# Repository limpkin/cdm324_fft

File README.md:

# CDM324 v2 FFT Project
This repository contains the source files created for the making of the CDM324 project described on <a href="https://www.limpkin.fr/index.php?post/2022/03/31/CDM324-Doppler-Motion-Sensor-Backpack%2C-now-with-FFTs%21">limpkin.fr</a>  
The assembly may be purchased here: <a href="https://www.tindie.com/products/stephanelec/cdm324-doppler-speed-sensor/">US shop</a> / <a href="https://lectronz.com/products/cdm324-doppler-speed-sensor">EU shop</a>   

## Repository Structure
- <b>datasheets</b>: main components datasheets
- <b>fw</b>: firmware source files, used in STM32CubeIDE
- <b>kicad</b>: kicad source files for the "backpack" (cdm324_v2) and the "expansion board" (cdm324_exp)
- <b>scripts</b>: python source files for the tools that are used together with the expansion board

## Quick Interfacing Guide (to be completed)

### Unit change to km/h  
To change the speed readout to km/h, connect the "PA1/KMH" pad to the "GND" pad in the above diagram.  

### UART connection  
**The UART connection is 3V3 and NOT 5V.**  
To connect the device to an external platform through UART, please use the MCU UART RX/TX pins shown above.   
The baud rate is **1Mbit/s**, speed **can be queried** by **sending the 'k'** character for km/h or the 'm' character for mph.  
**In case of doubt about the UART connection, reboot the device**: it should output "CDM324 fw....".  
**Make sure your host device can handle 1MBit/s**. If that's not the case, head to the [release section](https://github.com/limpkin/cdm324_fft/releases) to download firmware with different UART baud rates.  
Finally, if you still have doubts about the UART connection, you may connect one of your host platform GPIO to the nRESET pin and reset the CDM324 device at your host platform boot.  

## Reflashing the Device

In the unlikely case you want to reflash your device with another firmware, you may either use the [GUI present in this repository](https://github.com/limpkin/cdm324_fft/tree/main/scripts) or the [stm32loader python module](https://pypi.org/project/stm32loader/) directly :  

> pip install stm32loader
> 
... then with the expansion board connected to the device (**as it uses RTS/CTS signals to control the MCU nRESET and BOOT0 pins**):  

> stm32loader -b 115200 -p  com_port -e -w -v -s -f F3 updatefile.bin

If you don't have the companion expansion board, you may use [STM32 Flash loader](https://www.st.com/en/development-tools/flasher-stm32.html) after performing the following toggling sequence:  
- tie nRESET to GND  
- bring BOOT0 to 3V3_OUT  
- release nRESET  
- releae BOOT0  

## Sample Arduino code to fetch speed from device

```c
#define RESET_PIN 2

void issue_cdm324_reset()
{  
  bool string_received = false;
  char receive_buffer[50];
  int index = 0;

  // 20ms reset
  pinMode(RESET_PIN, OUTPUT);
  delay(20);
  pinMode(RESET_PIN, INPUT);

  // get string
  while (string_received == false)
  {
    if (Serial1.available() > 0)
    {
      char bla = Serial1.read();
      receive_buffer[index++] = bla;
      if (bla == '\n')
        string_received = true;
    }
  }
  receive_buffer[index] = 0;

  Serial.println("Received from the CDM324:");
  Serial.println(receive_buffer);
}

void setup() 
{
  // Local console
  Serial.begin(115200);
  Serial.println("Hello there!");

  // To the CDM324
  Serial1.begin(57600);

  // Reset CDM324
  pinMode(RESET_PIN, INPUT);
  digitalWrite(RESET_PIN, LOW);
  issue_cdm324_reset();
}

float get_speed(bool kmh)
{
  if (kmh == true)
  {
    // Query km/h * 10
    Serial1.print('k');
  }
  else
  {
    // Query mph * 10
    Serial1.print('m');
  }  
  while(Serial1.available() == 0);
  float speed = Serial1.parseFloat();
  return (speed / 10);
}

void loop()
{
  Serial.println(get_speed(false));
  delay(500);
}
```

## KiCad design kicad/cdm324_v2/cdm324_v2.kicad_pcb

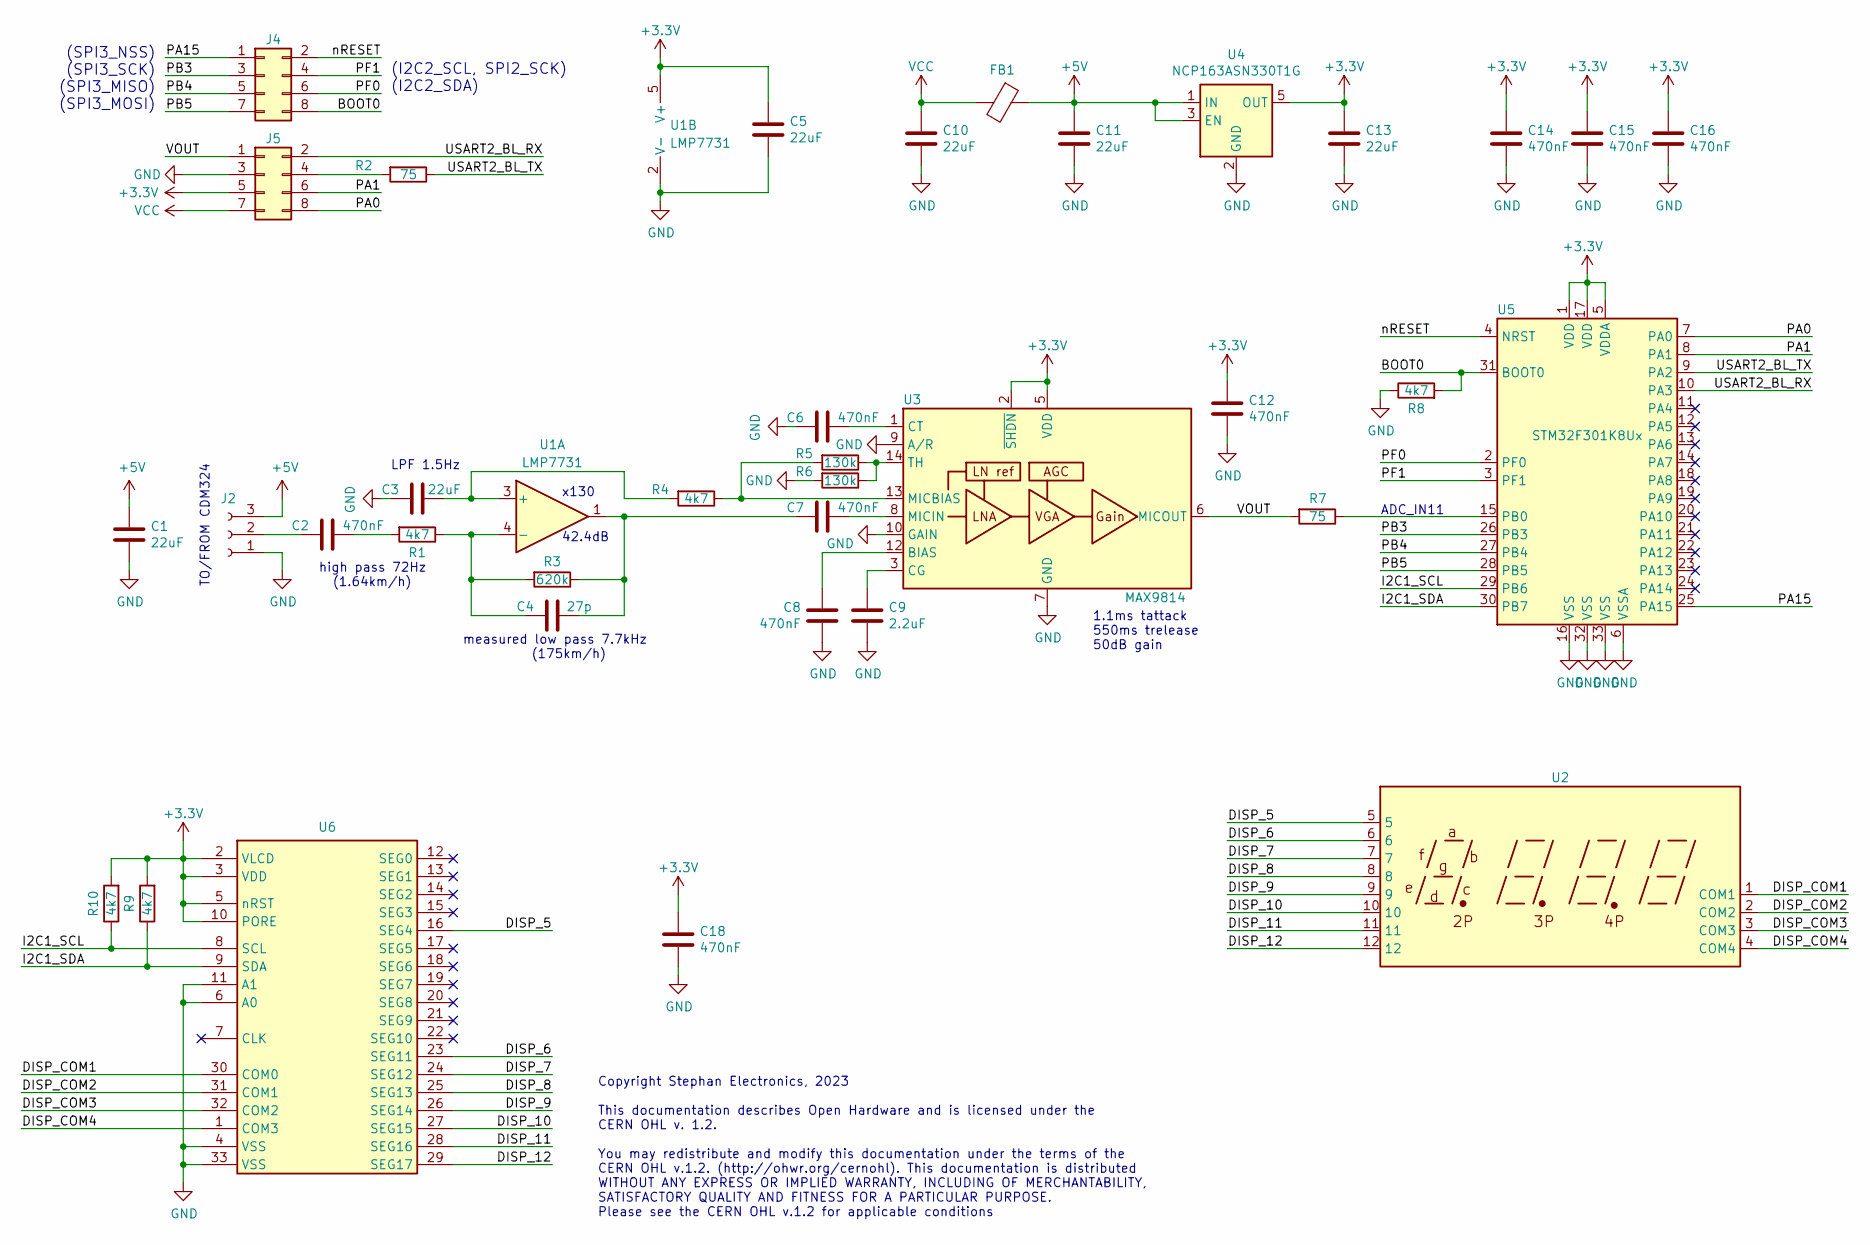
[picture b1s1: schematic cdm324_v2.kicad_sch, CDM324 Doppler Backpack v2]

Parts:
C1, C3, C5, C10, C11, C13: 22uF; C_0805_2012Metric
C2, C6, C7, C8, C12, C14, C15, C16, C18: 470nF; C_0402_1005Metric
C4: 27p; C_0603_1608Metric
C9: 2.2uF; C_0603_1608Metric
FB1: Ferrite_Bead; L_0805_2012Metric
J2: Conn_01x03_Female; PinHeader_1x03_P2.54mm_Vertical
J4, J5: Conn_02x04_Odd_Even; PinSocket_2x04_P2.54mm_Vertical
R1, R4, R8, R9, R10: 4k7; R_0603_1608Metric
R2, R7: 75; R_0402_1005Metric
R3: 620k; R_0603_1608Metric
R5, R6: 130k; R_0603_1608Metric
U1: LMP7731; SOT-23-5
U2: TN_DISPLAY
U3: MAX9814; DFN-14-1EP_3x3mm_P0.4mm_EP1.78x2.35mm
U4: NCP163ASN330T1G; SOT-23-5
U5: STM32F301K8Ux; QFN-32-1EP_5x5mm_P0.5mm_EP3.45x3.45mm
U6: QFN-32-1EP_5x5mm_P0.5mm_EP3.65x3.65mm

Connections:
+3V3: C5.1, C12.1, C13.1, C14.1, C15.1, C16.1, C18.1, J5.5, R9.2, R10.2, U1.5 (V+), U3.2 (~SHDN), U3.5 (VDD), U4.5 (OUT), U5.1 (VDD), U5.5 (VDDA), U5.17 (VDD), U6.2 (VLCD), U6.3 (VDD), U6.5 (nRST), U6.10 (PORE)
+5V: C1.1, C11.1, FB1.1, J2.3, U4.1 (IN), U4.3 (EN)
/BOOT0: J4.8, R8.2, U5.31 (BOOT0)
/DISP_5: U2.5, U6.16 (SEG4)
/DISP_6: U2.6, U6.23 (SEG11)
/DISP_7: U2.7, U6.24 (SEG12)
/DISP_8: U2.8, U6.25 (SEG13)
/DISP_9: U2.9, U6.26 (SEG14)
/DISP_10: U2.10, U6.27 (SEG15)
/DISP_11: U2.11, U6.28 (SEG16)
/DISP_12: U2.12, U6.29 (SEG17)
/DISP_COM1: U2.1 (COM1), U6.30 (COM0)
/DISP_COM2: U2.2 (COM2), U6.31 (COM1)
/DISP_COM3: U2.3 (COM3), U6.32 (COM2)
/DISP_COM4: U2.4 (COM4), U6.1 (COM3)
/I2C1_SCL: R10.1, U5.29 (PB6), U6.8 (SCL)
/I2C1_SDA: R9.1, U5.30 (PB7), U6.9 (SDA)
/PA0: J5.8, U5.7 (PA0)
/PA1: J5.6, U5.8 (PA1)
/PA15: J4.1, U5.25 (PA15)
/PB3: J4.3, U5.26 (PB3)
/PB4: J4.5, U5.27 (PB4)
/PB5: J4.7, U5.28 (PB5)
/PF0: J4.6, U5.2 (PF0)
/PF1: J4.4, U5.3 (PF1)
/USART2_BL_RX: J5.2, U5.10 (PA3)
/USART2_BL_TX: R2.1, U5.9 (PA2)
/VOUT: J5.1, R7.2, U3.6 (MICOUT)
/nRESET: J4.2, U5.4 (NRST)
GND: C1.2, C3.2, C5.2, C6.2, C8.2, C9.2, C10.2, C11.2, C12.2, C13.2, C14.2, C15.2, C16.2, C18.2, J2.1, J5.3, R6.2, R8.1, U1.2 (V-), U3.4 (GND), U3.7 (GND), U3.9 (A/R), U3.10 (GAIN), U3.11 (GND), U3.15 (GND), U4.2 (GND), U5.6 (VSSA), U5.16 (VSS), U5.32 (VSS), U5.33 (VSS), U6.4 (VSS), U6.6 (A0), U6.11 (A1), U6.33 (VSS)
unnamed: C2.1, R1.2
unnamed: C4.1, C7.2, R3.1, U1.1
unnamed: C2.2, J2.2
unnamed: J5.4, R2.2
unnamed: C3.1, R4.2, U1.3 (+)
unnamed: C4.2, R1.1, R3.2, U1.4 (-)
unnamed: C8.1, U3.12 (BIAS)
unnamed: C9.1, U3.3 (CG)
unnamed: C6.1, U3.1 (CT)
unnamed: R4.1, R5.2, U3.13 (MICBIAS)
unnamed: C7.1, U3.8 (MICIN)
unnamed: R5.1, R6.1, U3.14 (TH)
unnamed: R7.1, U5.15 (PB0)
VCC: C10.1, FB1.2, J5.7

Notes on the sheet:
1.1ms tattack 550ms trelease 50dB gain
measured low pass 7.7kHz (175km/h)
(SPI3_NSS) (SPI3_SCK) (SPI3_MISO) (SPI3_MOSI)
TO/FROM CDM324
Copyright Stephan Electronics, 2023 This documentation describes Open Hardware and is licensed under the CERN OHL v. 1.2. You may redistribute and modify this documentation under the terms of the CERN OHL v.1.2. (http://ohwr.org/cernohl). This documentation is distributed WITHOUT ANY EXPRESS OR IMP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
ADC_IN11
x130
high pass 72Hz (1.64km/h)
LPF 1.5Hz
42.4dB
(I2C2_SCL, SPI2_SCK) (I2C2_SDA)

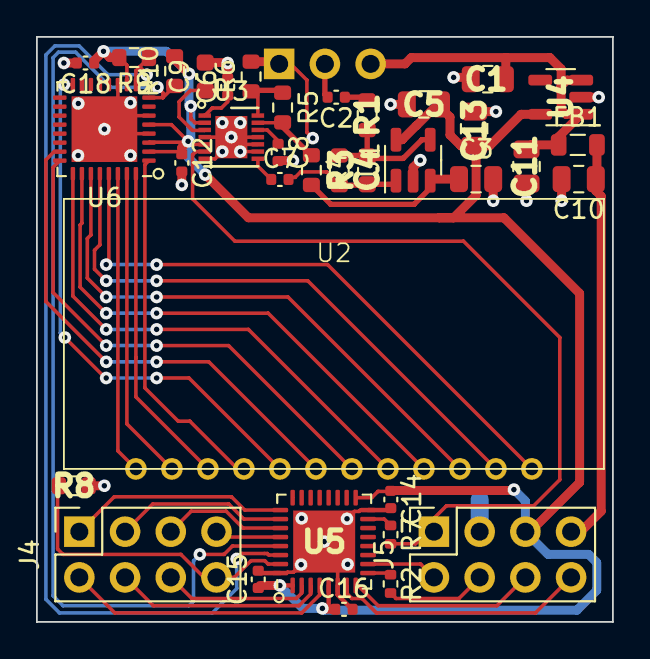
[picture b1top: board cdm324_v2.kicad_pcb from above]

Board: 2 copper layers, 32.0 x 32.5 mm, 37 parts (1 on the bottom side), 44 nets.

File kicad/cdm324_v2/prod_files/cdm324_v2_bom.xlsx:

Item # | Qty | Designator | Value | Manufacturer | Manufacturer Part Number | Alternative LCSC part number | Package/Footprint | Digikey Link
1 | 6 | C1, C3, C5, C10, C11, C13 | 22uF | Samsung Electro-Mechanics | CL21A226MOCLRNC | C602037 | 0805 | https://www.digikey.com/product-detail/en/samsung-electro-me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
2 | 1 | C4 | 200p | Samsung Electro-Mechanics | CL10C201JB8NNNC | C107080 | 0603 | https://www.digikey.com/product-detail/en/samsung-electro-me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
3 | 9 | C2, C6, C7, C8, C12, C14, C15, C16, C18 | 470nF | TDK Corporation | C1005X5R1E474K050BB | C92361 | 0402 | https://www.digikey.com/en/products/detail/tdk-corporation/C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
4 | 1 | C9 | 2.2uF | Murata Electronics | GRM188R71A225KE15D | C1607 | 0603 | https://www.digikey.com/en/products/detail/murata-electronic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
5 | 1 | FB1 | Ferrite_Bead | Laird-Signal Integrity Products | HZ0805D102R-10 | C44838 |  | http://www.digikey.com/product-detail/en/HZ0805D102R-10/240-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
6 | 1 | J2 | Conn_01x03_Female | Sullins Connector Solutions | PPPC031LFBN-RC | C146243 |  | http://www.digikey.com/product-detail/en/sullins-connector-s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
7 | 2 | J4, J5 | Conn_02x04_Odd_Even | Sullins Connector Solutions | PPPC042LFBN-RC | C92271 |  | https://www.digikey.com/en/products/detail/sullins-connector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
8 | 5 | R1, R4, R8, R9, R10 | 4k7 | YAGEO | RC0603FR-074K7L | C99782 | 0603 | https://www.digikey.com/en/products/detail/yageo/RC0603FR-07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
9 | 2 | R2, R7 | 75 | YAGEO | RC0402JR-0775RL | C137841 | 0402 | https://www.digikey.com/en/products/detail/yageo/RC0402JR-07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
10 | 3 | R3, R5, R6 | 130k | Panasonic Electronic Components | ERJ-3EKF1303V | C163432 | 0603 | https://www.digikey.com/product-detail/en/panasonic-electron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
11 | 1 | U1 | LMP7731 | Texas Instruments | LMP7731MF/NOPB | C202252 |  | https://www.digikey.ch/en/products/detail/texas-instruments/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
12 | 1 | U3 | MAX9814 | Analog Devices Inc./Maxim Integrated | MAX9814ETD+T | C41714 |  | https://www.digikey.com/en/products/detail/analog-devices-in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
13 | 1 | U4 | NCP163ASN330T1G | onsemi | NCP163ASN330T1G | C603656 |  | https://www.digikey.com/product-detail/en/on-semiconductor/N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
14 | 1 | U5 | STM32F301K8Ux | STMicroelectronics | STM32F301K8U6 | C111684 |  | https://www.digikey.com/product-detail/en/stmicroelectronics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
15 | 1 | U6 | PCA8561AHN/AY | NXP USA Inc. | PCA8561AHN/AY | C2653710 |  | https://www.digikey.ch/en/products/detail/nxp-usa-inc/PCA856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
16 | 1 | U2 | 12PIN TN Positive 4-Digits |  |  |  |  | https://www.aliexpress.com/item/1005003060952508.html

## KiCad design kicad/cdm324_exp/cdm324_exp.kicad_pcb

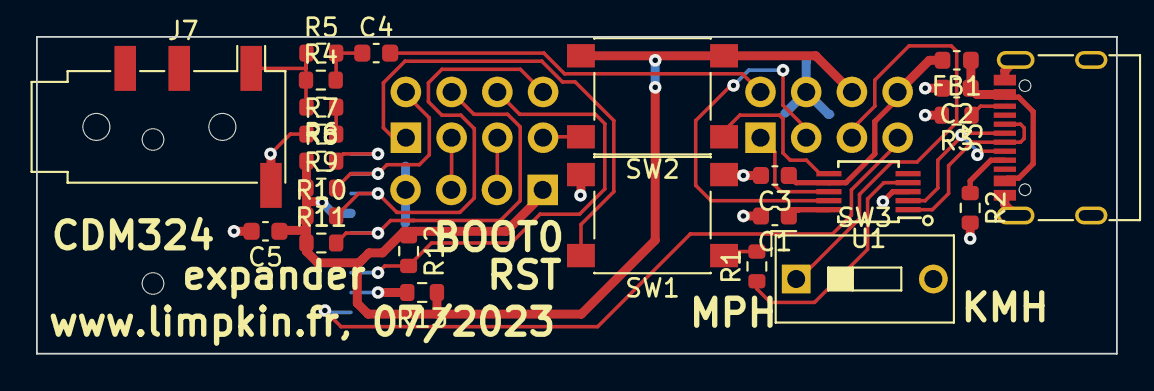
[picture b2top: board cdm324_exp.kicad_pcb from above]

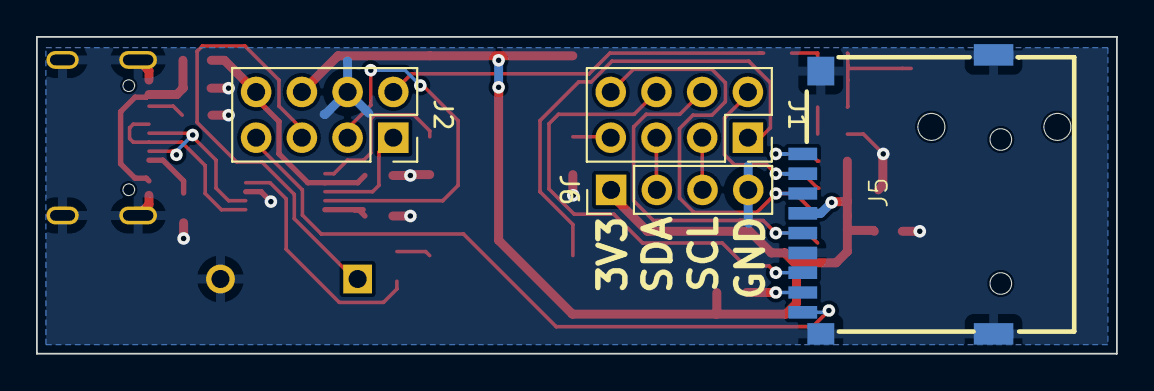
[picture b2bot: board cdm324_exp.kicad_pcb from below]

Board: 2 copper layers, 60.0 x 17.6 mm, 29 parts (4 on the bottom side), 28 nets.

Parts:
C1, C2, C3, C4, C5: 1uF; C_0603_1608Metric
FB1: FerriteBead; L_0603_1608Metric
J1, J2: Conn_02x04_Odd_Even; PinSocket_2x04_P2.54mm_Vertical
J3: USB_C_Receptacle_USB2.0; USB_C_Receptacle_G-Switch_GT-USB-7010ASV
J5: Micro_SD_Card_Det1; XKTF-015-N
J6: Conn_01x04_Socket; PinHeader_1x04_P2.54mm_Vertical
J7: AudioJack4; Jack_3.5mm_PJ320D_Horizontal
R1, R4, R5, R6, R7: 1k; R_0603_1608Metric
R2, R3: 5.1k; R_0603_1608Metric
R8, R9, R10, R11, R12, R13: 49k9; R_0603_1608Metric
SW1, SW2: SW_Push; SW_Push_1P1T_NO_6x6mm_H9.5mm
SW3: SW_DIP_x01; SW_DIP_SPSTx01_Slide_9.78x4.72mm_W7.62mm_P2.54mm
U1: CH340X; MSOP-10_3x3mm_P0.5mm

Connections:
+3V3: C5.1, J2.6, J5.4 (VDD), J6.1, R8.1, R9.1, R10.1, R11.1, R12.1, R13.1, SW2.2
/BOOT0: J1.7, SW2.1, U1.6 (TNOW)
/I2C_SCL: J1.3, J6.3
/I2C_SDA: J1.5, J6.2
/PA0: J2.7, J5.9 (DET)
/PA1: J2.5, SW3.1
/SPI_MISO: J1.6, J5.7 (DAT0), R12.2
/SPI_MOSI: J1.8, J5.3 (CMD), R10.2
/SPI_SCK: J1.4, J5.5 (CLK), R11.2
/SPI_nCS: J1.2, J5.2 (DAT3/CD), R9.2
/UART_RX: J2.1, U1.8 (TXD)
/UART_TX: J2.3, U1.9 (RXD)
/VOUT: C4.2, J2.2
/nRESET: J1.1, R1.2, SW1.1
GND: C1.2, C2.2, C3.2, C5.2, J2.4, J3.A1 (GND), J3.A12 (GND), J3.B1 (GND), J3.B12 (GND), J3.S1 (SHIELD), J5.6 (VSS), J5.10 (SHIELD), J6.4, J7.S, R2.2, R3.2, R7.1, SW1.2, SW3.2, U1.3 (GND)
unnamed: C2.1, FB1.1, J3.A4 (VBUS), J3.A9 (VBUS), J3.B4 (VBUS), J3.B9 (VBUS)
unnamed: C4.1, R4.2, R5.2
unnamed: J3.A5 (CC1), R2.1
unnamed: J3.B5 (CC2), R3.1
unnamed: J5.8 (DAT1), R13.2
unnamed: J5.1 (DAT2), R8.2
unnamed: J7.T, R4.1, R5.1, R6.2
unnamed: R6.1, R7.2
unnamed: J3.A6 (D+), J3.B6 (D+), U1.1 (UD+)
unnamed: J3.A7 (D-), J3.B7 (D-), U1.2 (UD-)
unnamed: C1.1, U1.10 (V3)
unnamed: R1.1, U1.4 (~RTS)
VCC: C3.1, FB1.2, J2.8, U1.7 (VCC)

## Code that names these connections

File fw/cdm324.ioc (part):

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Mcu.Name=STM32F301K(6-8)Ux
Mcu.Package=UFQFPN32
Mcu.UserName=STM32F301K8Ux
PA0.Signal=GPIO_Input
PA1.Signal=GPIO_Input
PA15.Signal=GPIO_Output
PA2.Mode=Asynchronous
PA2.Signal=USART2_TX
PA3.Mode=Asynchronous
PA3.Signal=USART2_RX
PB0.GPIOParameters=GPIO_Label
PB0.GPIO_Label=DOPPLER
PB0.Mode=IN11-Single-Ended
PB0.Signal=ADC1_IN11
PB3.Mode=Full_Duplex_Master
PB3.Signal=SPI3_SCK
PB4.Mode=Full_Duplex_Master
PB4.Signal=SPI3_MISO
PB5.Mode=Full_Duplex_Master
PB5.Signal=SPI3_MOSI
PB6.Mode=I2C
PB6.Signal=I2C1_SCL
PB7.Mode=I2C
PB7.Signal=I2C1_SDA
RCC.HSEPLLFreq_Value=8000000
RCC.HSE_VALUE=8000000
RCC.SYSCLKFreq_VALUE=64000000
RCC.SYSCLKSourceVirtual=RCC_SYSCLKSOURCE_PLLCLK
board=custom

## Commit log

2023-07-31 update gitignore
2023-07-31 documentation
2023-07-31 documentation update
2023-07-31 blank ini
2023-07-31 doc update
2023-08-05 first stage changed, POR for segment controller
2023-08-08 correct resistor divider for jack output
2023-08-15 kmh/mph switch, sd card writing tested
2023-08-23 adding picture
2023-09-29 problematic gitignore fix
2023-10-15 explansion board schematics in pdf format
2023-10-29 sample arduino code
2024-08-04 Add python requirements file
2024-08-21 3D printed plastic holder file upload, fix #13
